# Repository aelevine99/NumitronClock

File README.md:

# NumitronClock

## Project Overview
This project uses soviet IV-12 tubes (they were easier to find than actual Numitrons) for a fun, retro-inspired desk clock. The project is split into two main parts for modularity: a breakout board that can drive 2 tubes, and a control board with 2 outputs for breakout boards. I will update this description and provide documentation as the project evolves.

## NUMITRONS!

"Advert for RCA NUMITRON Display Devices". Electronic Design. 22 (12). Hayden: 163. 1974-06-07.

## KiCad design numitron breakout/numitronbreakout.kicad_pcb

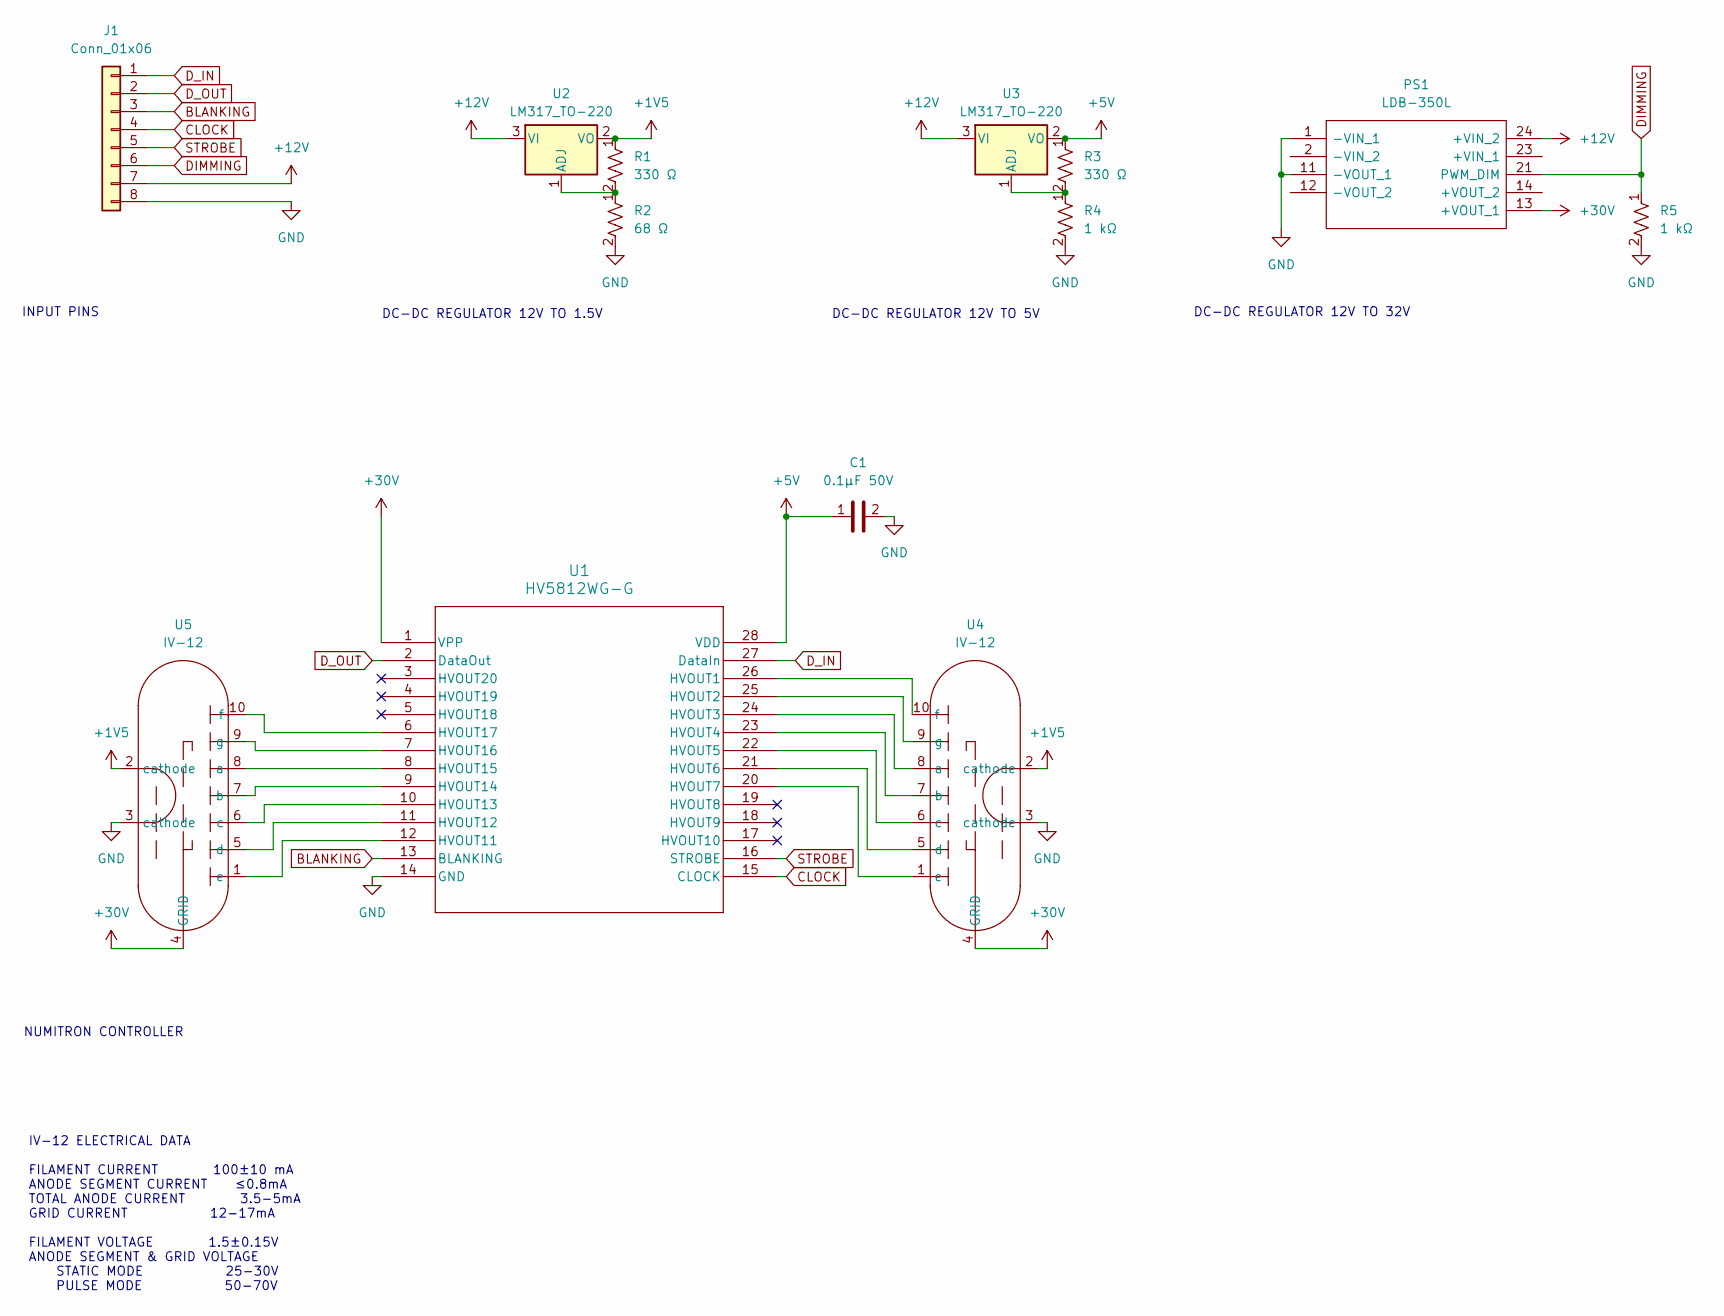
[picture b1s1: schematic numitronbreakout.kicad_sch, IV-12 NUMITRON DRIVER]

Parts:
C1: 0.1μF 50V; C_1206_3216Metric_Pad1.33x1.80mm_HandSolder; Manufacturer_Part_Number CL31B104KBCNNNC
J1: Conn_01x06; 66100811722; Manufacturer_Part_Number 66100811722
PS1: LDB-350L; LDB600L; Part No LDB-500L
R1, R3: 330 Ω; R_1206_3216Metric_Pad1.30x1.75mm_HandSolder; Part No CRCW0402240RFKED
R2: 68 Ω; R_1206_3216Metric_Pad1.30x1.75mm_HandSolder; Part No CRCW040248R7FKED
R4, R5: 1 kΩ; R_1206_3216Metric_Pad1.30x1.75mm_HandSolder; Part No CRCW040248R7FKED
U1: HV5812WG-G; SOW28_17P90X7P50_MCH; Part No HV5812WG-G
U2, U3: LM317_TO-220; TO-220-3_Vertical; Part No LM317TNS/NOPB-ND
U4, U5: IV-12; iv-12

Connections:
+1V5: R1.1, U2.2 (VO), U4.2 (cathode), U5.2 (cathode)
+5V: C1.1, R3.1, U1.28 (VDD), U3.2 (VO)
+12V: J1.7, PS1.24 (+VIN_2), U2.3 (VI), U3.3 (VI)
+30V: PS1.13 (+VOUT_1), U1.1 (VPP), U4.4 (GRID), U5.4 (GRID)
BLANKING: J1.3, U1.13 (BLANKING)
CLOCK: J1.4, U1.15 (CLOCK)
DIMMING: J1.6, PS1.21 (PWM_DIM), R5.1
D_IN: J1.1, U1.27 (DataIn)
D_OUT: J1.2, U1.2 (DataOut)
GND: C1.2, J1.8, PS1.1 (-VIN_1), PS1.11 (-VOUT_1), R2.2, R4.2, R5.2, U1.14 (GND), U4.3 (cathode), U5.3 (cathode); also elsewhere on the board
unnamed: U1.26 (HVOUT1), U4.10 (f)
unnamed: U1.25 (HVOUT2), U4.9 (g)
unnamed: U1.24 (HVOUT3), U4.8 (a)
unnamed: U1.23 (HVOUT4), U4.7 (b)
unnamed: U1.22 (HVOUT5), U4.6 (c)
unnamed: U1.21 (HVOUT6), U4.5 (d)
unnamed: U1.20 (HVOUT7), U4.1 (e)
unnamed: U1.12 (HVOUT11), U5.1 (e)
unnamed: U1.11 (HVOUT12), U5.5 (d)
unnamed: U1.10 (HVOUT13), U5.6 (c)
unnamed: U1.9 (HVOUT14), U5.7 (b)
unnamed: U1.8 (HVOUT15), U5.8 (a)
unnamed: U1.7 (HVOUT16), U5.9 (g)
unnamed: U1.6 (HVOUT17), U5.10 (f)
unnamed: R1.2, R2.1, U2.1 (ADJ)
unnamed: R3.2, R4.1, U3.1 (ADJ)
STROBE: J1.5, U1.16 (STROBE)

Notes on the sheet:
INPUT PINS
DC-DC REGULATOR 12V TO 1.5V
DC-DC REGULATOR 12V TO 32V
DC-DC REGULATOR 12V TO 5V
NUMITRON CONTROLLER
IV-12 ELECTRICAL DATA FILAMENT CURRENT 100±10 mA ANODE SEGMENT CURRENT ≤0.8mA TOTAL ANODE CURRENT 3.5-5mA GRID CURRENT 12-17mA FILAMENT VOLTAGE 1.5±0.15V ANODE SEGMENT & GRID VOLTAGE STATIC MODE 25-30V PULSE MODE 50-70V

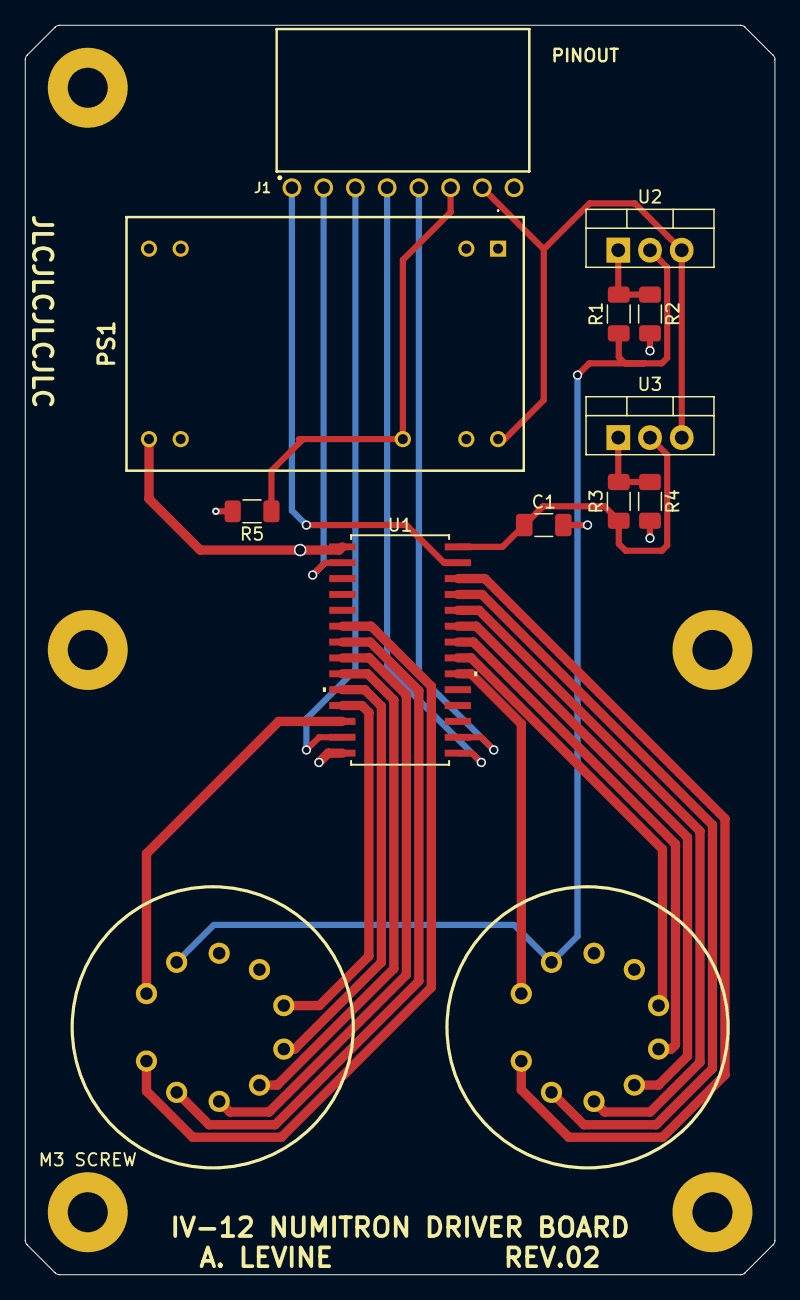
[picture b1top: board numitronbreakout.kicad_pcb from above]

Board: 4 copper layers, 60.0 x 100.0 mm, 14 parts (0 on the bottom side), 27 nets.

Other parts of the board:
M3 SCREW: MountingHole_3.2mm_M3_Pad

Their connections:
GND: M3 SCREW.1; also elsewhere on the board

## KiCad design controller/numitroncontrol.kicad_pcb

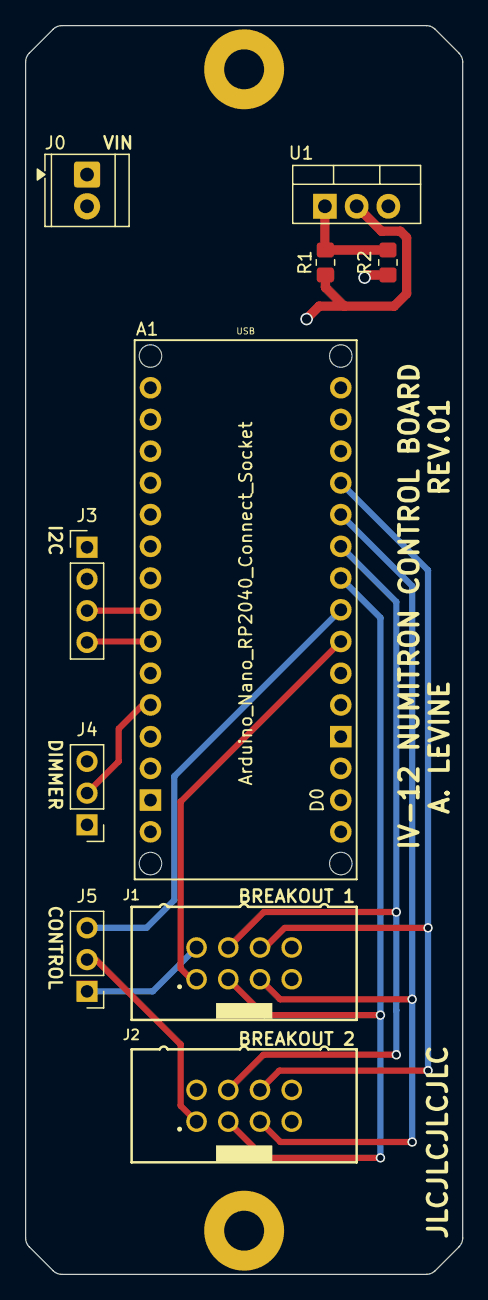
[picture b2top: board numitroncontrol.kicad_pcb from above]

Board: 4 copper layers, 35.0 x 100.0 mm, 10 parts (0 on the bottom side), 16 nets.

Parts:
A1: Arduino_Nano_RP2040_Connect_Socket; Arduino_Nano_Every_Socket
J0: Screw_Terminal_01x02; TerminalBlock_TE_282834-2_1x02_P2.54mm_Horizontal
J1, J2: Conn_01x06; 61200821621
J3: I2C; PinHeader_1x04_P2.54mm_Vertical
J4: Screw_Terminal_01x03; PinHeader_1x03_P2.54mm_Vertical
J5: Conn_01x03_Pin; PinHeader_1x03_P2.54mm_Vertical
R1: 390 Ω; R_0805_2012Metric_Pad1.20x1.40mm_HandSolder
R2: 3.3 kΩ; R_0805_2012Metric_Pad1.20x1.40mm_HandSolder
U1: LM317_TO-220; TO-220-3_Vertical

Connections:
+3V3: A1.3V3 (3.3V), J3.2, J4.3
+12V: A1.VIN, J1.7, J2.7, R1.1, U1.2 (VO)
BLANKING: A1.D6, J1.3, J2.3
CLOCK: A1.D7, J1.4, J2.4
DIMMING: A1.D9, J1.6, J2.6
D_IN1: A1.D4, J1.1
D_IN2: A1.D5, J5.3
D_OUT1: J1.2, J5.1
GND: A1.GND1 (GND), A1.GND2 (GND), J0.2, J1.8, J2.8, J3.1, J4.1, R2.2
unnamed: J0.1, U1.3 (VI)
unnamed: J2.1, J5.2
unnamed: R1.2, R2.1, U1.1 (ADJ)
POT: A1.A7, J4.2
SCL: A1.A5 (A5/SCL), J3.4
SDA: A1.A4 (A4/SDA), J3.3
STROBE: A1.D8, J1.5, J2.5

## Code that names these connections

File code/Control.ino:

/*

Control for Nixie Clock
Al Levine

*/

// ~~~~~~~~~~ HARDWARE PIN DEFINITIONS ~~~~~~~~~~
#define SCL A5	//i2c SCL
#define SDA A4	//i2c SDA
#define DIN 5	//Data in 2 (minutes)
#define BLNK 6	//Blanking
#define CLK 7	//Clock
#define STR 8	//Strobe
#define DIM 9	//Dimming PWM
#define POT A7	//Potentiometer input

//Bit array for 2x HV5812 chips
boolean nixieDisplayArray[40];

//Assignment of tube cathodes to HV8512 driver pins
/*
Left digit:					Right digit:
Tube	HV5812WG-G			Tube	HV5812WG-G
01/e	12/HVOUT11			01/e	20/HVOUT7
05/d	11/HVOUT12			05/d	21/HVOUT6
06/c	10/HVOUT13			06/c	22/HVOUT5
07/b	09/HVOUT14			07/b	23/HVOUT4
08/a	08/HVOUT15			08/a	24/HVOUT3
09/g	07/HVOUT16			09/g	25/HVOUT2
10/f	06/HVOUT17			10/f	26/HVOUT1
*/

//	cathode	 01,05,06,07,08,09,10
int tube1[]={12,11,10,09,08,07,06}; // do i use the pin number or the hvout number????
int tube2[]={20,21,22,23,24,25,26};

int digit1, digit2, digit3, digit4


// ~~~~~~~~~~ SETUP ~~~~~~~~~~
void setup() {
	Serial.begin(9600);
}

// ~~~~~~~~~~ LOOP ~~~~~~~~~~
void loop() {
}

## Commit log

2024-07-07 init
2024-08-04 added tube, shift register
2024-08-05 added controller
2024-09-01 shift register wiring cleanup
2024-09-03 added voltage regulators, changed bit register
2024-09-06 Updated driver breakout and selected boost IC
2024-09-09 boost converter circuit populated, simplified wiring
2024-09-10 library cleanup
2024-09-10 began pcb layout
2024-10-28 boost converter refactor
    new design from web bench to reduce bom complexity & increase efficiency
2024-10-28 pcb layout
2024-10-31 finished wiring everything but 30v
2024-11-01 finally decided v boost solution, finished pathing pcb
2024-11-01 increased resistor size, generated gerbers for fab
2024-11-07 updated pin connector, layout
2024-11-07 fixed 3d model
2024-11-07 Create LICENSE
2024-11-12 updated boost converter and added dimming capability
2024-11-12 added mounting holes
2024-11-12 grounded mounting holes
2024-11-12 Small routing fix
2024-11-12 gerber update
2024-11-13 started controller schematic
2024-11-14 updated trace widths and did some renders
2024-11-16 minor pcb layout updates
2024-11-19 arduino pinout
2024-12-07 production files for rev1 order
2024-12-13 updated power supply
2024-12-20 continued design work on controller
2025-01-20 finished controller schematic, started pcb
2025-01-21 control pcb finished
2025-01-21 control pcb edits
2025-01-21 production files
2025-01-21 played tetris on pcb and re-exported prod files
2025-01-21 more pcb edits
2025-02-03 fixed serial communication pins
2025-02-03 updated documentation
2025-02-03 pin mapping
2025-02-04 Update LICENSE
    MIT to GNU
2025-07-12 updated control board
2025-07-17 replaced pot with screw terminal for flexible mounting
2025-07-18 code attempt, small layout updates
2025-07-20 more code
2025-07-21 more code updates- font table and some basic functions
2025-07-22 Added jumper for control schemes
    can have discrete or daisy control of second output on control board
2025-07-22 code update
2025-07-22 updated gitignore
2025-07-23 semicolons
2025-07-23 control board layout tweaks
2025-07-23 more controller layout updates
2025-07-23 layout updates, gerbers generated
2025-07-23 gerber fix
2025-07-24 code fixes
    I have no idea what I'm doing :)
2025-07-24 fixed dimming issue
    dimming pwm signal was connected to the wrong pin (VOUT2 instead of PWM_DIM) on the meanwell power supply.
2025-07-31 updated breakout board gerbers
